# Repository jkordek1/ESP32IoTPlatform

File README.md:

# ESP32IoTPlatform

## What is it?
ESP32IoTPlatform is an open source platform aimed towards students at Zagreb University of Applied Sciences who will take the IoT course.
It enables quick and easy firmware development thanks to built in sensors, actuators and other electronic components.

## Features
- Based on dual-core ESP32 microcontroller module
- External battery connector
- Battery charging via microUSB cable
- Buzzer for audio queues
- HC-SR04 ultrasonic sensor connector
- MOSFET output
- Relay output
- LDR
- Potentiometer
- 1.3" OLED screen
- microSD slot
- accelerometer & gyro
- BME280 temperature and humidity sensor
- GPS module
- WS2812-B RGB LEDs
- Touchad
- Joypad

## Images

## Project folder structure
    .
    ├── ...
    ├── Images                  # Images of the project
    ├── Output files            # Gerber files
    ├── KiCadFiles              # Main folder
    │   ├── 3d modeli           # 3D models of added components
    │   ├── Board2Pdf           # Assembly files
    │   ├── bom                 # ibom assembly files
    │   └── gerber              # gerber
    ├── Schematic.pdf           # Schematic .pdf file
    └── ...

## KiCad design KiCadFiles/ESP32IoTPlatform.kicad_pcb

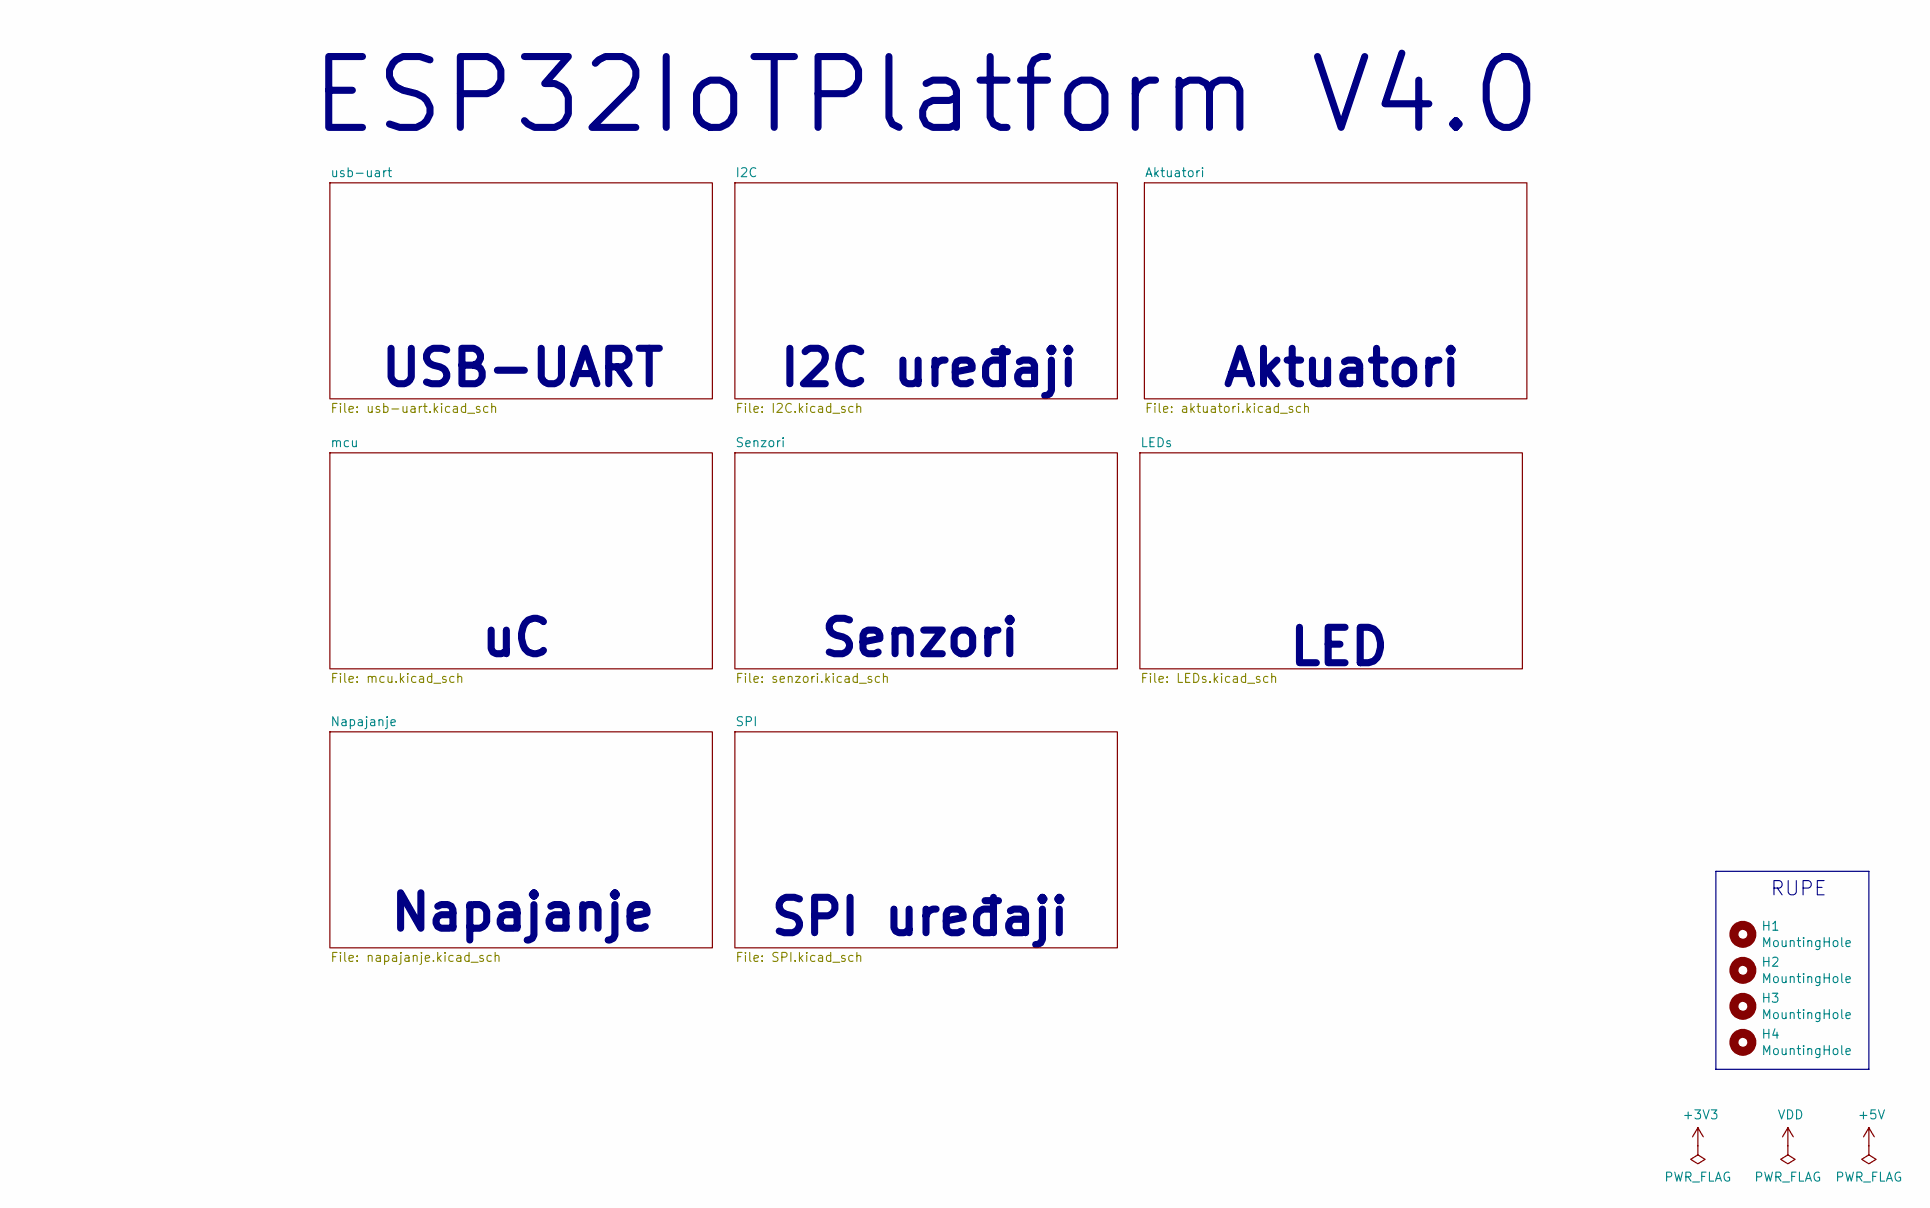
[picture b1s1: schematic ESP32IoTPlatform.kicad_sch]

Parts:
H1, H2, H3, H4: MountingHole; MountingHole_3.2mm_M3_Pad_Via_edited

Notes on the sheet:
RUPE
LED
Aktuatori
Senzori
Napajanje
SPI uređaji
ESP32IoTPlatform V4.0
I2C uređaji
USB-UART

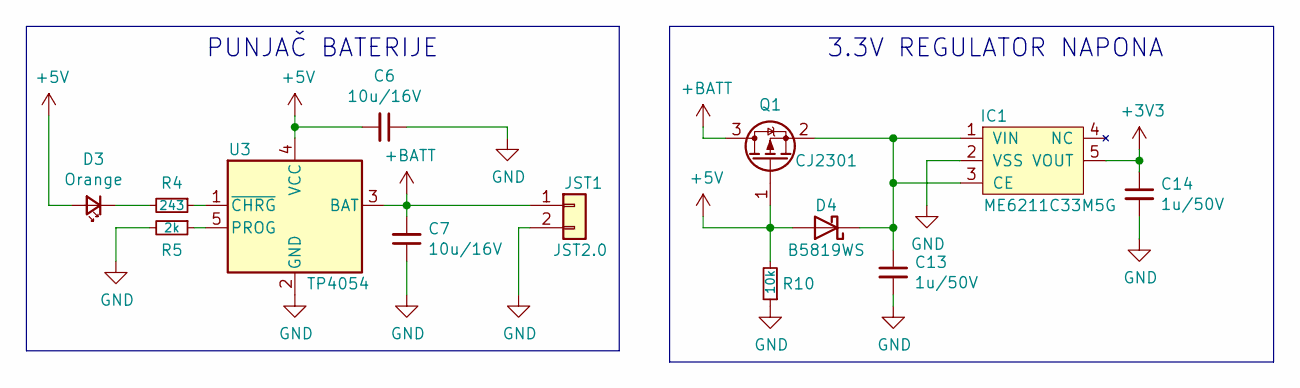
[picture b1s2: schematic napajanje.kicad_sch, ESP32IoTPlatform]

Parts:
C6, C7: 10u/16V; C_0805_2012Metric
C13, C14: 1u/50V; C_0805_2012Metric
D3: Orange; LED_0805_2012Metric
D4: B5819WS; D_SOD-323
IC1: ME6211C33M5G; SOT-23-5
JST1: JST2.0; A2001WR-S-2P_JST2.0
Q1: CJ2301; SOT-23
R4: 243; R_0805_2012Metric
R5: 2k; R_0805_2012Metric
R10: 10k; R_0805_2012Metric
U3: TP4054; TSOT-23-5

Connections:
+3V3: C14.1, IC1.5 (VOUT); also elsewhere on the board
+5V: C6.2, D3.2 (A), D4.2 (A), Q1.1 (G), R10.2, U3.4 (VCC); also elsewhere on the board
+BATT: C7.2, JST1.1, Q1.3 (D), U3.3 (BAT)
GND: C6.1, C7.1, C13.2, C14.2, IC1.2 (VSS), JST1.2, R5.2, R10.1, U3.2 (GND); also elsewhere on the board
unnamed: C13.1, D4.1 (K), IC1.1 (VIN), IC1.3 (CE), Q1.2 (S)
unnamed: D3.1 (K), R4.2
unnamed: R4.1, U3.1 (~CHRG)
unnamed: R5.1, U3.5 (PROG)

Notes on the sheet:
3.3V REGULATOR NAPONA
PUNJAČ BATERIJE

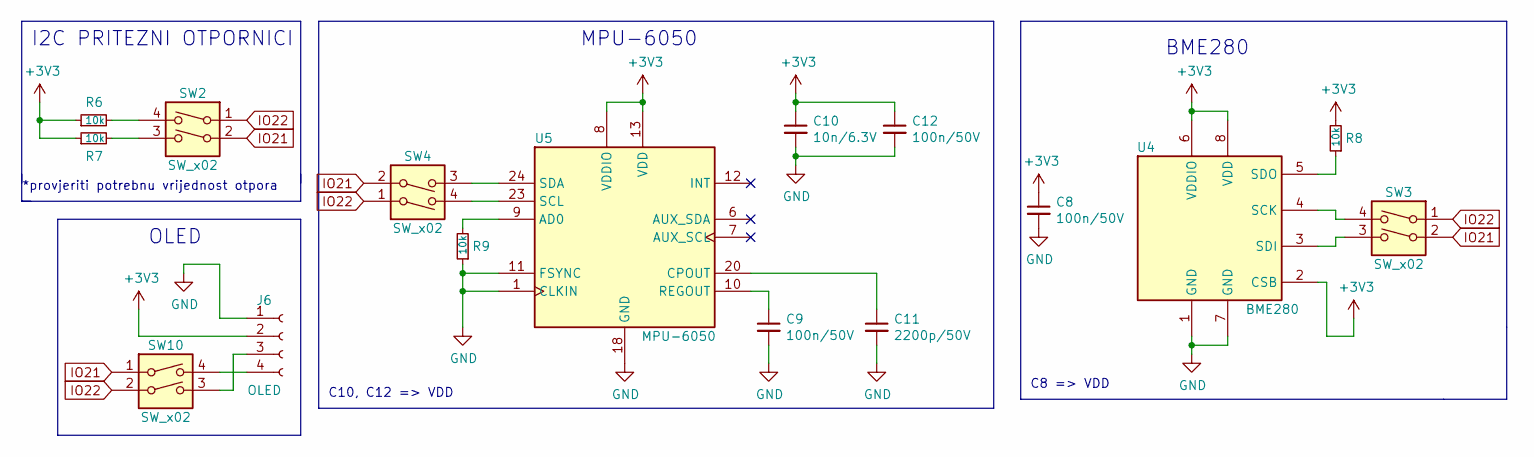
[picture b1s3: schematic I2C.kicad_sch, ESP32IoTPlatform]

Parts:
C8, C9, C12: 100n/50V; C_0805_2012Metric
C10: 10n/6.3V; C_0805_2012Metric
C11: 2200p/50V; C_0805_2012Metric
J6: OLED
R6, R7, R8, R9: 10k; R_0805_2012Metric
SW2, SW3, SW4, SW10: SW_x02; SW_DIP_SPSTx02_Slide_6.7x6.64mm_W6.73mm_P2.54mm_LowProfile_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
U4: BME280; Bosch_LGA-8_2.5x2.5mm_P0.65mm_ClockwisePinNumbering
U5: MPU-6050; InvenSense_QFN-24_4x4mm_P0.5mm

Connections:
+3V3: C8.1, C10.1, C12.1, J6.2, R6.1, R7.1, R8.2, U4.2 (CSB), U4.6 (VDDIO), U4.8 (VDD), U5.8 (VDDIO), U5.13 (VDD); also elsewhere on the board
GND: C8.2, C9.2, C10.2, C11.2, C12.2, J6.1, R9.1, U4.1 (GND), U4.7 (GND), U5.1 (CLKIN), U5.11 (FSYNC), U5.18 (GND); also elsewhere on the board
IO21: SW2.2, SW3.2, SW4.2, SW10.1; also elsewhere on the board
IO22: SW2.1, SW3.1, SW4.1, SW10.2; also elsewhere on the board
unnamed: C9.1, U5.10 (REGOUT)
unnamed: C11.1, U5.20 (CPOUT)
unnamed: J6.3, SW10.3
unnamed: J6.4, SW10.4
unnamed: R6.2, SW2.4
unnamed: R7.2, SW2.3
unnamed: R8.1, U4.5 (SDO)
unnamed: R9.2, U5.9 (AD0)
unnamed: SW3.3, U4.3 (SDI)
unnamed: SW3.4, U4.4 (SCK)
unnamed: SW4.3, U5.24 (SDA)
unnamed: SW4.4, U5.23 (SCL)

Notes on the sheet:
BME280
*provjeriti potrebnu vrijednost otpora
OLED
I2C PRITEZNI OTPORNICI
C8 => VDD
MPU-6050
C10, C12 => VDD

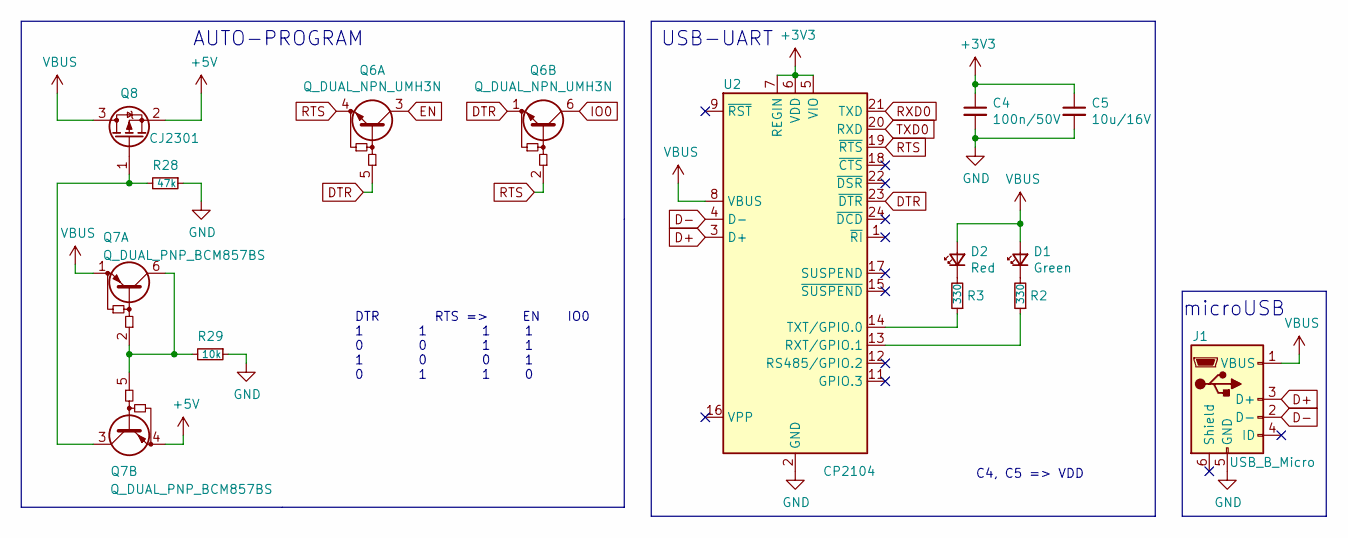
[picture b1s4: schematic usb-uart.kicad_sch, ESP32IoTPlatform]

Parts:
C4: 100n/50V; C_0805_2012Metric
C5: 10u/16V; C_0805_2012Metric
D1: Green; LED_0805_2012Metric
D2: Red; LED_0805_2012Metric
J1: USB_B_Micro; USB_Micro-AB_Molex_47590-0001
Q6: Q_DUAL_NPN_UMH3N; SOT-363_SC-70-6
Q7: Q_DUAL_PNP_BCM857BS; SOT-363_SC-70-6
Q8: CJ2301; SOT-23
R2, R3: 330; R_0805_2012Metric
R28: 47k; R_0805_2012Metric
R29: 10k; R_0805_2012Metric
U2: CP2104; QFN-24-1EP_4x4mm_P0.5mm_EP2.6x2.6mm

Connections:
+3V3: C4.1, C5.1, U2.5 (VIO), U2.6 (VDD), U2.7 (REGIN); also elsewhere on the board
+5V: Q7.4 (E2), Q8.2 (S); also elsewhere on the board
D+: J1.3 (D+), U2.3 (D+)
D-: J1.2 (D-), U2.4 (D-)
DTR: Q6.1 (E1), Q6.5 (B1), U2.23 (~DTR)
EN: Q6.3 (C1); also elsewhere on the board
GND: C4.2, C5.2, J1.5 (GND), R28.1, R29.1, U2.2 (GND), U2.25 (GND); also elsewhere on the board
IO0: Q6.6 (C1); also elsewhere on the board
unnamed: D1.1 (K), R2.2
unnamed: D2.1 (K), R3.2
unnamed: Q7.2 (B1), Q7.5 (B2), Q7.6 (C1), R29.2
unnamed: Q7.3 (C2), Q8.1 (G), R28.2
unnamed: R2.1, U2.13 (RXT/GPIO.1)
unnamed: R3.1, U2.14 (TXT/GPIO.0)
RTS: Q6.2 (B1), Q6.4 (E1), U2.19 (~RTS)
RXD0: U2.21 (TXD); also elsewhere on the board
TXD0: U2.20 (RXD); also elsewhere on the board
VBUS: D1.2 (A), D2.2 (A), J1.1 (VBUS), Q7.1 (E1), Q8.3 (D), U2.8 (VBUS)

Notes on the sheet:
AUTO-PROGRAM
C4, C5 => VDD
USB-UART
DTR RTS => EN IO0 1 1 1 1 0 0 1 1 1 0 0 1 0 1 1 0
microUSB

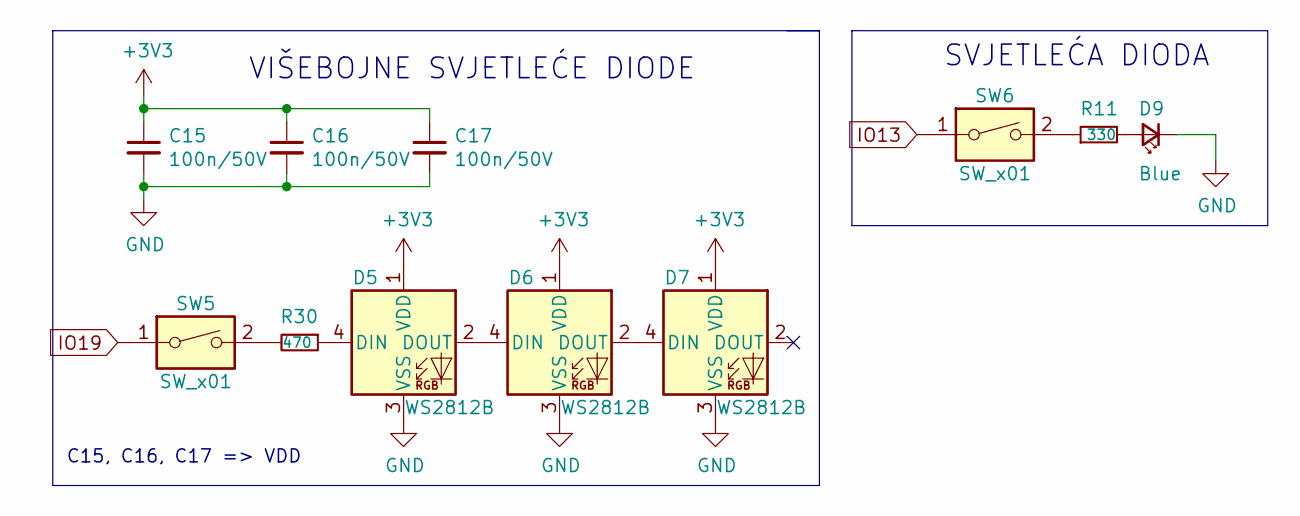
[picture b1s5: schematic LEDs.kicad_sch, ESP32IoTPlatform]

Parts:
C15, C16, C17: 100n/50V; C_0805_2012Metric
D5, D6, D7: WS2812B; LED_WS2812B_PLCC4_5.0x5.0mm_P3.2mm
D9: Blue; LED_1206_3216Metric
R11: 330; R_0805_2012Metric
R30: 470; R_0805_2012Metric
SW5, SW6: SW_x01; SW_DIP_SPSTx01_Slide_6.7x4.1mm_W6.73mm_P2.54mm_LowProfile_J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

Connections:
+3V3: C15.1, C16.1, C17.1, D5.1 (VDD), D6.1 (VDD), D7.1 (VDD); also elsewhere on the board
GND: C15.2, C16.2, C17.2, D5.3 (VSS), D6.3 (VSS), D7.3 (VSS), D9.1 (K); also elsewhere on the board
IO13: SW6.1; also elsewhere on the board
IO19: SW5.1; also elsewhere on the board
unnamed: D5.2 (DOUT), D6.4 (DIN)
unnamed: D5.4 (DIN), R30.1
unnamed: D6.2 (DOUT), D7.4 (DIN)
unnamed: D9.2 (A), R11.2
unnamed: R11.1, SW6.2
unnamed: R30.2, SW5.2

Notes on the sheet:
SVJETLEĆA DIODA
VIŠEBOJNE SVJETLEĆE DIODE
C15, C16, C17 => VDD

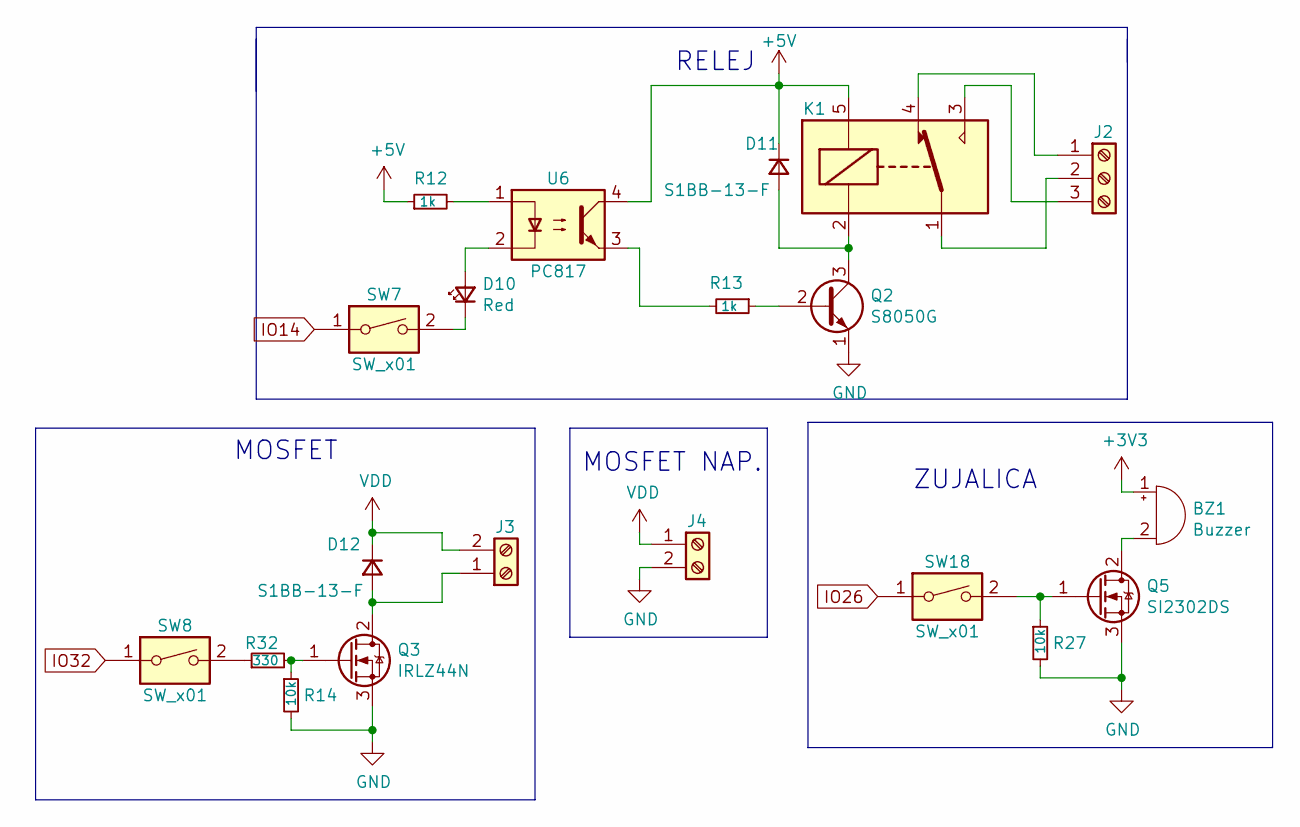
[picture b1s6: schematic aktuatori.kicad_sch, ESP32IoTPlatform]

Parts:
BZ1: Buzzer; PS1240P02BT
D10: Red; LED_0805_2012Metric
D11, D12: S1BB-13-F; D_SMA
J2: Screw_Terminal_01x03; TerminalBlock_Phoenix_MKDS-1,5-3-5.08_1x03_P5.08mm_Horizont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
J3, J4: Screw_Terminal_01x02; TerminalBlock_Phoenix_MKDS-1,5-2-5.08_1x02_P5.08mm_Horizont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
K1: SANYOU_SRD_Form_C; Relay_SPDT_SANYOU_SRD_Series_Form_C
Q2: S8050G; SOT-23
Q3: IRLZ44N; TO-220-3_Vertical
Q5: SI2302DS; SOT-23
R12, R13: 1k; R_0805_2012Metric
R14, R27: 10k; R_0805_2012Metric
R32: 330; R_0805_2012Metric
SW7, SW8, SW18: SW_x01; SW_DIP_SPSTx01_Slide_6.7x4.1mm_W6.73mm_P2.54mm_LowProfile_J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
U6: PC817; DIP-4_W7.62mm

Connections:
+3V3: BZ1.1 (-); also elsewhere on the board
+5V: D11.1 (K), K1.5, R12.1, U6.4; also elsewhere on the board
GND: J4.2, Q2.1 (E), Q3.3 (S), Q5.3 (S), R14.2, R27.2; also elsewhere on the board
IO14: SW7.1; also elsewhere on the board
IO26: SW18.1; also elsewhere on the board
IO32: SW8.1; also elsewhere on the board
unnamed: BZ1.2 (+), Q5.2 (D)
unnamed: D10.1 (K), SW7.2
unnamed: D10.2 (A), U6.2
unnamed: D11.2 (A), K1.2, Q2.3 (C)
unnamed: D12.2 (A), J3.1, Q3.2 (D)
unnamed: J2.1, K1.4
unnamed: J2.2, K1.1
unnamed: J2.3, K1.3
unnamed: Q2.2 (B), R13.1
unnamed: Q3.1 (G), R14.1, R32.2
unnamed: Q5.1 (G), R27.1, SW18.2
unnamed: R12.2, U6.1
unnamed: R13.2, U6.3
unnamed: R32.1, SW8.2
VDD: D12.1 (K), J3.2, J4.1

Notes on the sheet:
ZUJALICA
MOSFET NAP.
RELEJ
MOSFET

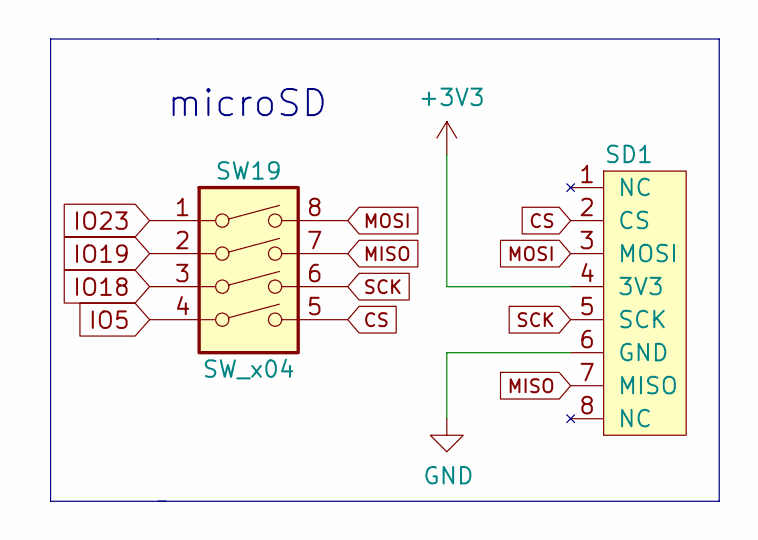
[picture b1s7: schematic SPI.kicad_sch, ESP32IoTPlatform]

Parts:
SD1: microSD-MOLEX-473521001; MOLEX_47352-1001
SW19: SW_x04; SW_DIP_SPSTx04_Slide_6.7x11.72mm_W6.73mm_P2.54mm_LowProfile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

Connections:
+3V3: SD1.4 (3V3); also elsewhere on the board
CS: SD1.2 (CS), SW19.5
GND: SD1.6 (GND); also elsewhere on the board
IO5: SW19.4; also elsewhere on the board
IO18: SW19.3; also elsewhere on the board
IO19: SW19.2; also elsewhere on the board
IO23: SW19.1; also elsewhere on the board
MISO: SD1.7 (MISO), SW19.7
MOSI: SD1.3 (MOSI), SW19.8
SCK: SD1.5 (SCK), SW19.6

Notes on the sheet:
microSD

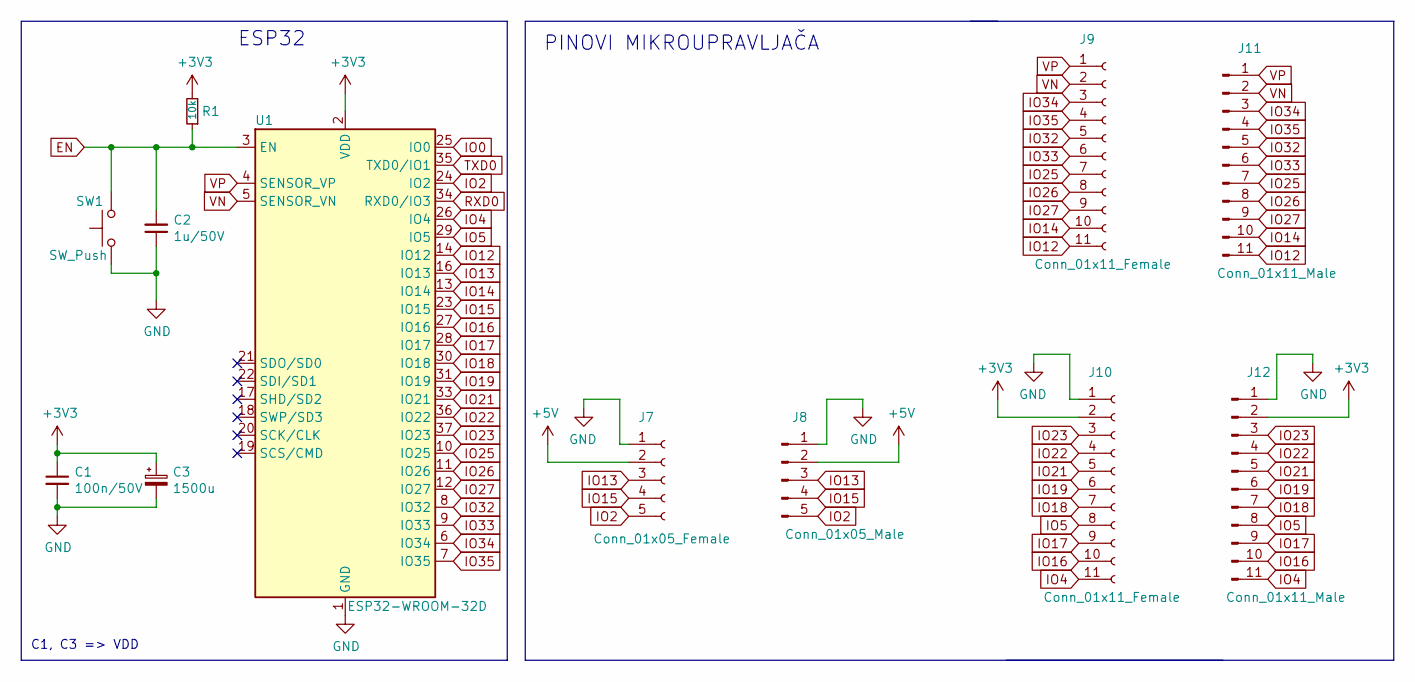
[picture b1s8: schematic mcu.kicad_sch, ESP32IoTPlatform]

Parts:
C1: 100n/50V; C_0805_2012Metric
C2: 1u/50V; C_0805_2012Metric
C3: 1500u; CP_EIA-7343-31_Kemet-D
J7: Conn_01x05_Female; PinSocket_1x05_P2.54mm_Vertical
J8: Conn_01x05_Male; PinHeader_1x05_P2.54mm_Vertical
J9, J10: Conn_01x11_Female; PinSocket_1x11_P2.54mm_Vertical
J11, J12: Conn_01x11_Male; PinHeader_1x11_P2.54mm_Vertical
R1: 10k; R_0805_2012Metric
SW1: SW_Push; SW_SPST_PTS645
U1: ESP32-WROOM-32D; ESP32-WROOM-32

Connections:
+3V3: C1.1, C3.1, J10.2, J12.2, R1.2, U1.2 (VDD); also elsewhere on the board
+5V: J7.2, J8.2; also elsewhere on the board
EN: C2.2, R1.1, SW1.2, U1.3 (EN); also elsewhere on the board
GND: C1.2, C2.1, C3.2, J7.1, J8.1, J10.1, J12.1, SW1.1, U1.1 (GND), U1.15 (GND), U1.38 (GND), U1.39 (GND); also elsewhere on the board
IO0: U1.25 (IO0); also elsewhere on the board
IO2: J7.5, J8.5, U1.24 (IO2); also elsewhere on the board
IO4: J10.11, J12.11, U1.26 (IO4); also elsewhere on the board
IO5: J10.8, J12.8, U1.29 (IO5); also elsewhere on the board
IO12: J9.11, J11.11, U1.14 (IO12)
IO13: J7.3, J8.3, U1.16 (IO13); also elsewhere on the board
IO14: J9.10, J11.10, U1.13 (IO14); also elsewhere on the board
IO15: J7.4, J8.4, U1.23 (IO15); also elsewhere on the board
IO16: J10.10, J12.10, U1.27 (IO16); also elsewhere on the board
IO17: J10.9, J12.9, U1.28 (IO17); also elsewhere on the board
IO18: J10.7, J12.7, U1.30 (IO18); also elsewhere on the board
IO19: J10.6, J12.6, U1.31 (IO19); also elsewhere on the board
IO21: J10.5, J12.5, U1.33 (IO21); also elsewhere on the board
IO22: J10.4, J12.4, U1.36 (IO22); also elsewhere on the board
IO23: J10.3, J12.3, U1.37 (IO23); also elsewhere on the board
IO25: J9.7, J11.7, U1.10 (IO25); also elsewhere on the board
IO26: J9.8, J11.8, U1.11 (IO26); also elsewhere on the board
IO27: J9.9, J11.9, U1.12 (IO27); also elsewhere on the board
IO32: J9.5, J11.5, U1.8 (IO32); also elsewhere on the board
IO33: J9.6, J11.6, U1.9 (IO33); also elsewhere on the board
IO34: J9.3, J11.3, U1.6 (IO34); also elsewhere on the board
IO35: J9.4, J11.4, U1.7 (IO35); also elsewhere on the board
RXD0: U1.34 (RXD0/IO3); also elsewhere on the board
TXD0: U1.35 (TXD0/IO1); also elsewhere on the board
VN: J9.2, J11.2, U1.5 (SENSOR_VN)
VP: J9.1, J11.1, U1.4 (SENSOR_VP)

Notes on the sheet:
ESP32
PINOVI MIKROUPRAVLJAČA
C1, C3 => VDD

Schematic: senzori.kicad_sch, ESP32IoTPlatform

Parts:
C19: 100n/50V; C_0805_2012Metric
C20: 10u/16V; C_0805_2012Metric
D13: Green; LED_0805_2012Metric
J5: Conn_01x04_Female; PinSocket_1x04_P2.54mm_Vertical
Q4: SI2302DS; SOT-23
R15: 1k; R_0805_2012Metric
R16: 1k5; R_0805_2012Metric
R17, R20: 10k; R_0805_2012Metric
R18: 470; R_0805_2012Metric
R19: LDR; R_LDR_7x6mm_P5.1mm_Vertical
R21: 243; R_0805_2012Metric
R22, R23, R24, R25, R26: 2k; R_0805_2012Metric
R31: 330; R_0805_2012Metric
RV1: 10k; Potentiometer_Bourns_3386P_Vertical
SW9: SW_x02; SW_DIP_SPSTx02_Slide_6.7x6.64mm_W6.73mm_P2.54mm_LowProfile_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
SW11: SW_x03; SW_DIP_SPSTx03_Slide_6.7x9.18mm_W6.73mm_P2.54mm_LowProfile_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
SW14, SW15, SW16: SW_x01; SW_DIP_SPSTx01_Slide_6.7x4.1mm_W6.73mm_P2.54mm_LowProfile_J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
SW17: SW_x05; SW_DIP_SPSTx05_Slide_6.7x14.26mm_W6.73mm_P2.54mm_LowProfile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
T1: SKRHABE010; Alps_SKRHABE010
TP1: Touchpad
U7: L80-M39

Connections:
+3V3: C19.1, C20.1, D13.2 (A), R19.1, R21.1, U7.4 (VCC), U7.5 (V_BCKP); also elsewhere on the board
+5V: J5.1; also elsewhere on the board
GND: C19.2, C20.2, J5.4, Q4.3 (S), R16.2, R17.2, R20.2, RV1.1, T1.5 (COMMON), U7.3 (GND), U7.12 (GND); also elsewhere on the board
IO2: SW17.3; also elsewhere on the board
IO4: SW16.1; also elsewhere on the board
IO5: SW11.1; also elsewhere on the board
IO15: SW17.4; also elsewhere on the board
IO16: SW11.3; also elsewhere on the board
IO17: SW11.2; also elsewhere on the board
IO18: SW17.2; also elsewhere on the board
IO23: SW17.1; also elsewhere on the board
IO25: SW17.5; also elsewhere on the board
IO27: SW9.2; also elsewhere on the board
IO33: SW9.1; also elsewhere on the board
IO34: SW15.1; also elsewhere on the board
IO35: SW14.1; also elsewhere on the board
unnamed: D13.1 (K), R18.2
unnamed: J5.2, SW9.3
unnamed: J5.3, R15.1
unnamed: Q4.1 (G), R17.1, R31.2
unnamed: Q4.2 (D), R18.1
unnamed: R15.2, R16.1, SW9.4
unnamed: R19.2, R20.1, SW14.2
unnamed: R21.2, RV1.3
unnamed: R22.1, T1.1 (A)
unnamed: R22.2, SW17.10
unnamed: R23.1, T1.2 (CENTER)
unnamed: R23.2, SW17.9
unnamed: R24.1, T1.3 (C)
unnamed: R24.2, SW17.8
unnamed: R25.1, T1.4 (B)
unnamed: R25.2, SW17.7
unnamed: R26.1, SW17.6
unnamed: R26.2, T1.6 (D)
unnamed: R31.1, U7.6 (1PPS)
unnamed: RV1.2, SW15.2
unnamed: SW11.4, U7.2 (TXD)
unnamed: SW11.5, U7.1 (RXD)
unnamed: SW11.6, U7.10 (~RESET)
unnamed: SW16.2, TP1.1

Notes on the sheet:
UPRAVLJAČKA RUČICA
FOTOOTPORNIK
UZ SENZOR UDALJENOSTI
GPS
POTENCIOMETAR
TOUCHPAD
C19, C20 => VCC

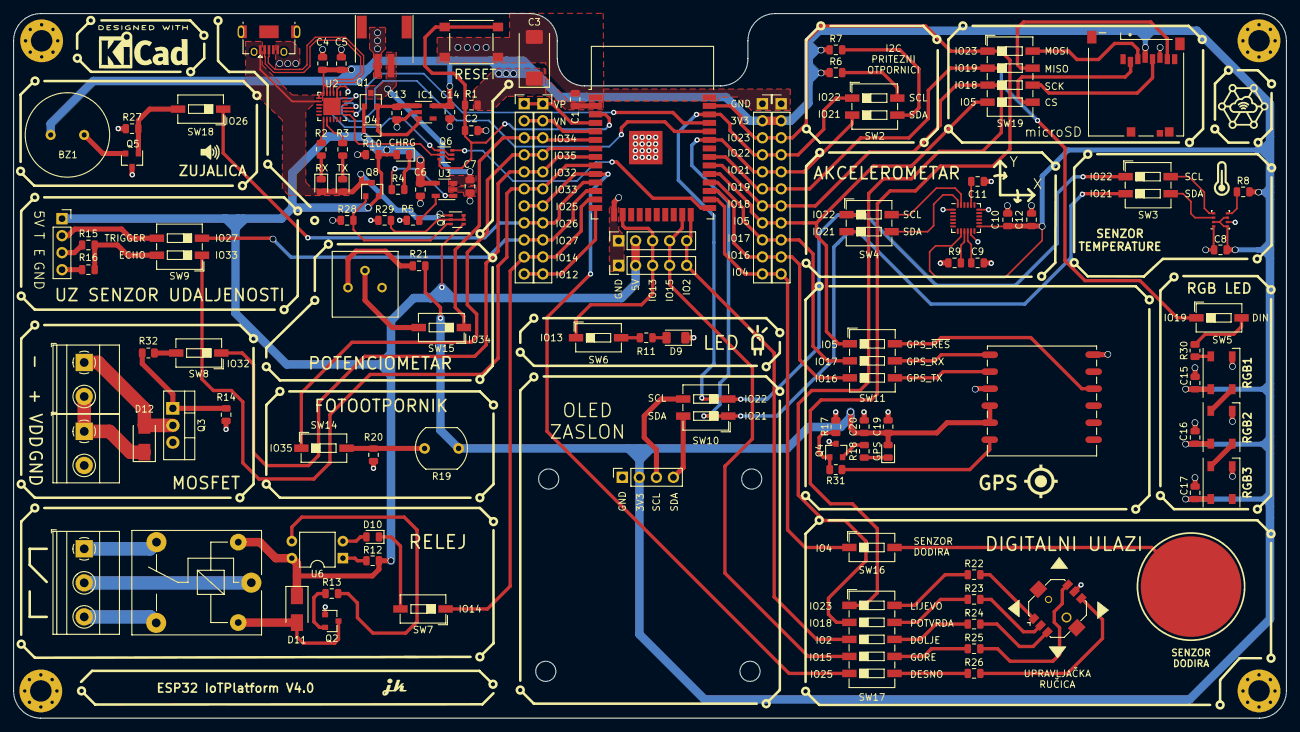
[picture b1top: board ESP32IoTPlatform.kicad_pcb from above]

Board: 2 copper layers, 190.0 x 105.2 mm, 119 parts (0 on the bottom side), 107 nets.

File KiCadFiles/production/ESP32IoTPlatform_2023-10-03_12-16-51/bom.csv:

Designator,Footprint,Quantity,Value,LCSC Part #
BZ1,PS1240P02BT,1,Buzzer,
"C1, C12, C15, C16, C17, C19, C4, C8, C9",0805,9,100n/50V,
C10,0805,1,10n/6.3V,
C11,0805,1,2200p/50V,
"C13, C14, C2",0805,3,1u/50V,
"C20, C5, C6, C7",0805,4,10u/16V,
C3,CP_EIA-7343-31_Kemet-D,1,1500u,
"D1, D13",0805,2,Green,
"D10, D2",0805,2,Red,
"D11, D12",D_SMA,2,S1BB-13-F,
D3,0805,1,Orange,
D4,D_SOD-323,1,B5819WS,
"D5, D6, D7",LED_WS2812B_PLCC4_5.0x5.0mm_P3.2mm,3,WS2812B,
D9,1206,1,Blue,
"H1, H2, H3, H4",MountingHole_3.2mm_M3_Pad_Via_edited,4,MountingHole,
IC1,SOT-23-5,1,ME6211C33M5G,
J1,USB_Micro-AB_Molex_47590-0001,1,USB_B_Micro,
"J10, J9",PinSocket_1x11_P2.54mm_Vertical,2,Conn_01x11_Female,
"J11, J12",PinHeader_1x11_P2.54mm_Vertical,2,Conn_01x11_Male,
J2,"TerminalBlock_Phoenix_MKDS-1,5-3-5.08_1x03_P5.08mm_Horizontal",1,Screw_Terminal_01x03,
"J3, J4","TerminalBlock_Phoenix_MKDS-1,5-2-5.08_1x02_P5.08mm_Horizontal",2,Screw_Terminal_01x02,
J5,PinSocket_1x04_P2.54mm_Vertical,1,Conn_01x04_Female,
J6,OLED,1,OLED,
J7,PinSocket_1x05_P2.54mm_Vertical,1,Conn_01x05_Female,
J8,PinHeader_1x05_P2.54mm_Vertical,1,Conn_01x05_Male,
JST1,A2001WR-S-2P_JST2.0,1,JST2.0,
K1,Relay_SPDT_SANYOU_SRD_Series_Form_C,1,SANYOU_SRD_Form_C,
"Q1, Q8",SOT-23,2,CJ2301,
Q2,SOT-23,1,S8050G,
Q3,TO-220-3_Vertical,1,IRLZ44N,
"Q4, Q5",SOT-23,2,SI2302DS,
Q6,SOT-363_SC-70-6,1,Q_DUAL_NPN_UMH3N,
Q7,SOT-363_SC-70-6,1,Q_DUAL_PNP_BCM857BS,
"R1, R10, R14, R17, R20, R27, R29, R6, R7, R8, R9",0805,11,10k,
"R11, R2, R3, R31, R32",0805,5,330,
"R12, R13, R15",0805,3,1k,
R16,0805,1,1k5,
"R18, R30",0805,2,470,
R19,R_LDR_7x6mm_P5.1mm_Vertical,1,LDR,
"R21, R4",0805,2,243,
"R22, R23, R24, R25, R26, R5",0805,6,2k,
R28,0805,1,47k,
RV1,Potentiometer_Bourns_3386P_Vertical,1,10k,
SD1,MOLEX_47352-1001,1,microSD-MOLEX-473521001,
SW1,SW_SPST_PTS645,1,SW_Push,
"SW10, SW2, SW3, SW4, SW9",SW_DIP_SPSTx02_Slide_6.7x6.64mm_W6.73mm_P2.54mm_LowProfile_JPin,5,SW_x02,
SW11,SW_DIP_SPSTx03_Slide_6.7x9.18mm_W6.73mm_P2.54mm_LowProfile_JPin,1,SW_x03,
"SW14, SW15, SW16, SW18, SW5, SW6, SW7, SW8",SW_DIP_SPSTx01_Slide_6.7x4.1mm_W6.73mm_P2.54mm_LowProfile_JPin,8,SW_x01,
SW17,SW_DIP_SPSTx05_Slide_6.7x14.26mm_W6.73mm_P2.54mm_LowProfile_JPin,1,SW_x05,
SW19,SW_DIP_SPSTx04_Slide_6.7x11.72mm_W6.73mm_P2.54mm_LowProfile_JPin,1,SW_x04,
T1,Alps_SKRHABE010,1,SKRHABE010,
TP1,Touchpad,1,Touchpad,
U1,ESP32-WROOM-32,1,ESP32-WROOM-32D,
U2,QFN-24-1EP_4x4mm_P0.5mm_EP2.6x2.6mm,1,CP2104,
U3,TSOT-23-5,1,TP4054,
U4,Bosch_LGA-8_2.5x2.5mm_P0.65mm_ClockwisePinNumbering,1,BME280,
U5,InvenSense_QFN-24_4x4mm_P0.5mm,1,MPU-6050,
U6,DIP-4_W7.62mm,1,PC817,
U7,L80-M39,1,L80-M39,

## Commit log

2022-02-09 v3.0
2022-02-09 Images
2022-02-10 logos
2022-02-10 route
2022-02-10 route2
2022-02-10 final
2022-02-10 done
2022-02-10 v4.0
2022-02-10 3dmodel
2022-02-10 UZ model update
2022-02-11 Schematic added
2022-02-12 board2pdf
